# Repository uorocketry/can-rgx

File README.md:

# uORocketry CAN-RGX 2021

This is the uORocketry code for the 2021 Canadian Reduced Gravity Experiment Design Challenge (CAN-RGX).

This repository consists of the code of three components:
- Raspberry Pi (mainRPI.py): In charge of monitoring the experiment and controlling various components on user request.
- Control GUI (mainLaptop.py): Connects to the RPi and provides a GUI to the user for monitoring and controlling the experiment.
- Teensy (teensy/): Communicates with the RPi. Controls and monitors the motors and photodiodes.

Together, these components control and monitor a heater, motors, high-powered LEDs, and sensors. Here is an overview of all of those systems together:

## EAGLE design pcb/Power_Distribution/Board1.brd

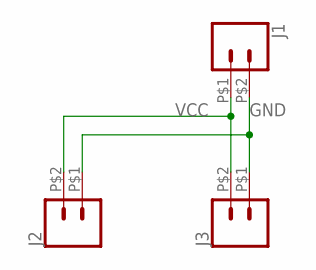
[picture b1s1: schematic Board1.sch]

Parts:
J1, J2, J3: CONN_02PTH2; 1X02_BIG

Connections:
GND: J1.P$2 (2), J2.P$1 (1), J3.P$1 (1)
VCC: J1.P$1 (1), J2.P$2 (2), J3.P$2 (2)

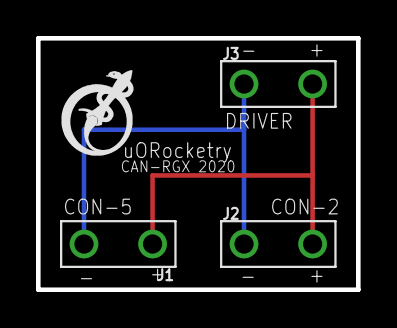
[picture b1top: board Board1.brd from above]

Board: 2 copper layers, 17.8 x 14.0 mm, 3 parts (0 on the bottom side), 2 nets.

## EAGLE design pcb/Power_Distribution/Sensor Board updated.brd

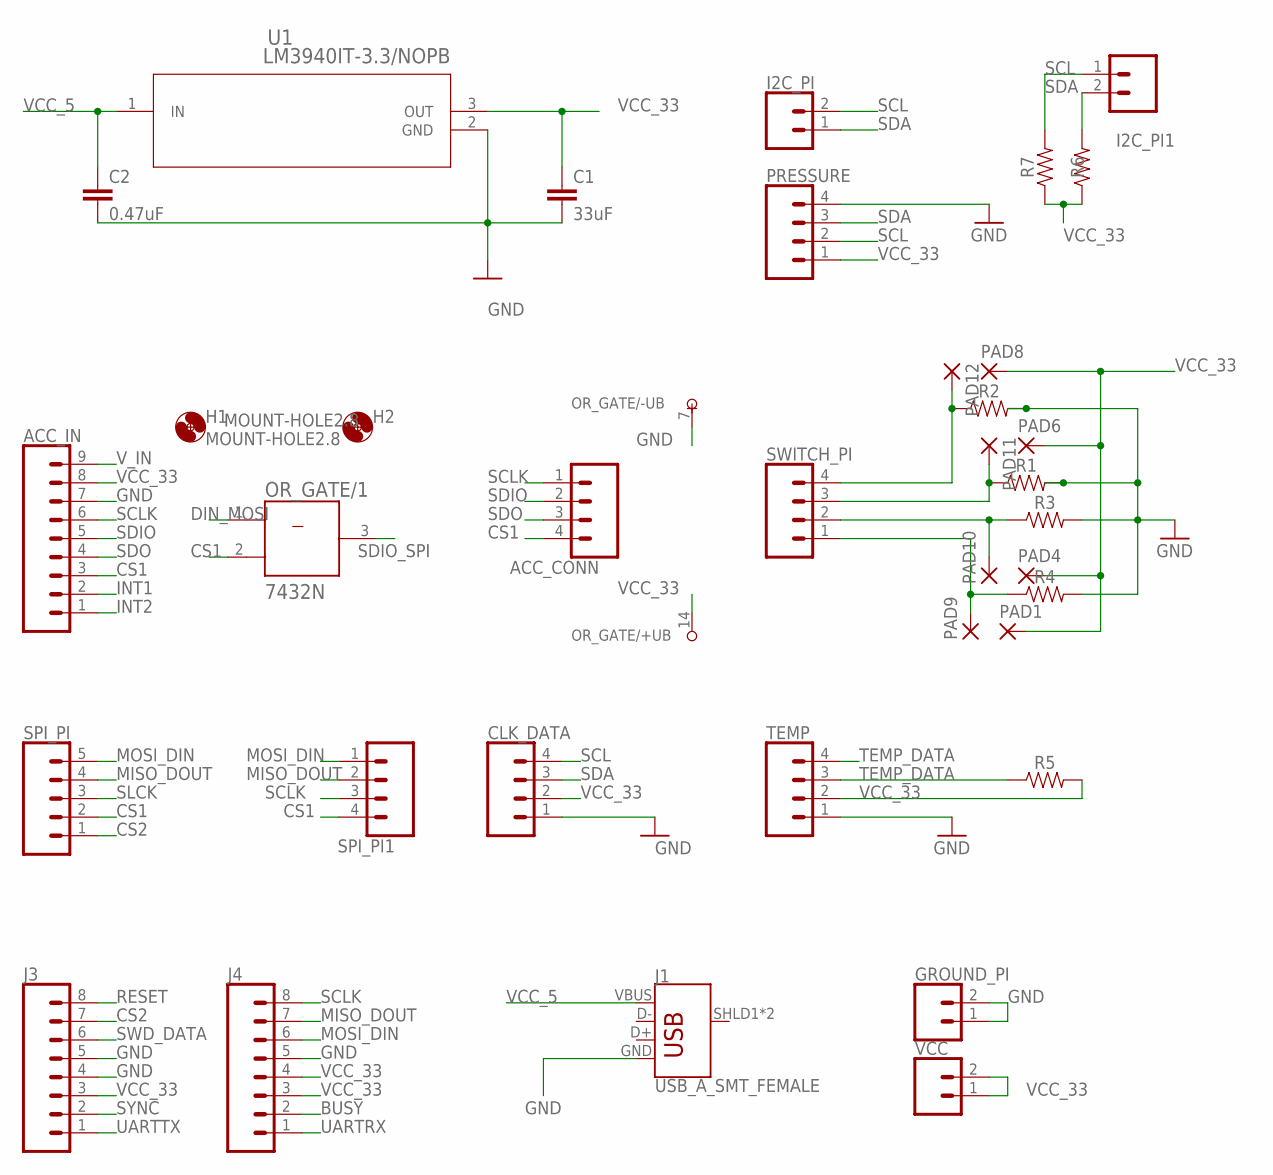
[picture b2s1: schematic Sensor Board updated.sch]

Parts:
ACC_CONN: CONN_04; 1X04
ACC_IN: CONN_09; 1X09
C1: 33uF; C2.5-4
C2: 0.47uF; C2.5-4
CLK_DATA: CONN_04; 1X04
GROUND_PI: CONN_02; 1X02
H1, H2: MOUNT-HOLE2.8; 2,8
I2C_PI, I2C_PI1: CONN_02; 1X02
J1: USB_A_SMT_FEMALE; USB-A-S-SILK-FEMALE
J3, J4: CONN_08"; 1X08
OR_GATE: 7432N; DIL14
PAD1, PAD4, PAD6, PAD8, PAD9, PAD10, PAD11, PAD12: 1,6/0,8
PRESSURE: CONN_04; 1X04
R1, R2, R3, R4, R5, R6, R7: AXIAL-0.3
SPI_PI: CONN_05; 1X05
SPI_PI1: CONN_04; 1X04
SWITCH_PI: CONN_04; 1X04
TEMP: CONN_04; 1X04
U1: LM3940IT-3.3/NOPB; T03B
VCC: CONN_02; 1X02

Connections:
BUSY: J4.2
CS1: ACC_CONN.4, ACC_IN.3, OR_GATE.2 (B), SPI_PI.2, SPI_PI1.4
CS2: J3.7, SPI_PI.1
DIN_MOSI: OR_GATE.1 (A)
GND: ACC_IN.7, C1.2, C2.2, CLK_DATA.1, GROUND_PI.1, GROUND_PI.2, J1.GND, J3.4, J3.5, J4.5, OR_GATE.7 (-UB), PRESSURE.4, R1.P$2 (2), R2.P$2 (2), R3.P$2 (2), R4.P$2 (2), TEMP.1, U1.2 (GND)
INT1: ACC_IN.2
INT2: ACC_IN.1
MISO_DOUT: J4.7, SPI_PI.4, SPI_PI1.2
MOSI_DIN: J4.6, SPI_PI.5, SPI_PI1.1
unnamed: PAD10.1, R3.P$1 (1), SWITCH_PI.2
unnamed: PAD9.1, R4.P$1 (1), SWITCH_PI.1
unnamed: PAD11.1, R1.P$1 (1), SWITCH_PI.3
unnamed: PAD12.1, R2.P$1 (1), SWITCH_PI.4
RESET: J3.8
SCL: CLK_DATA.4, I2C_PI.2, I2C_PI1.1, PRESSURE.2, R7.P$2 (2)
SCLK: ACC_CONN.1, ACC_IN.6, J4.8, SPI_PI1.3
SDA: CLK_DATA.3, I2C_PI.1, I2C_PI1.2, PRESSURE.3, R6.P$2 (2)
SDIO: ACC_CONN.2, ACC_IN.5
SDIO_SPI: OR_GATE.3 (Y)
SDO: ACC_CONN.3, ACC_IN.4
SLCK: SPI_PI.3
SWD_DATA: J3.6
SYNC: J3.2
TEMP_DATA: R5.P$1 (1), TEMP.3, TEMP.4
UARTRX: J4.1
UARTTX: J3.1
VCC_5: C2.1, J1.VBUS, U1.1 (IN)
VCC_33: ACC_IN.8, C1.1, CLK_DATA.2, J3.3, J4.3, J4.4, OR_GATE.14 (+UB), PAD1.1, PAD4.1, PAD6.1, PAD8.1, PRESSURE.1, R5.P$2 (2), R6.P$1 (1), R7.P$1 (1), TEMP.2, U1.3 (OUT), VCC.1, VCC.2
V_IN: ACC_IN.9

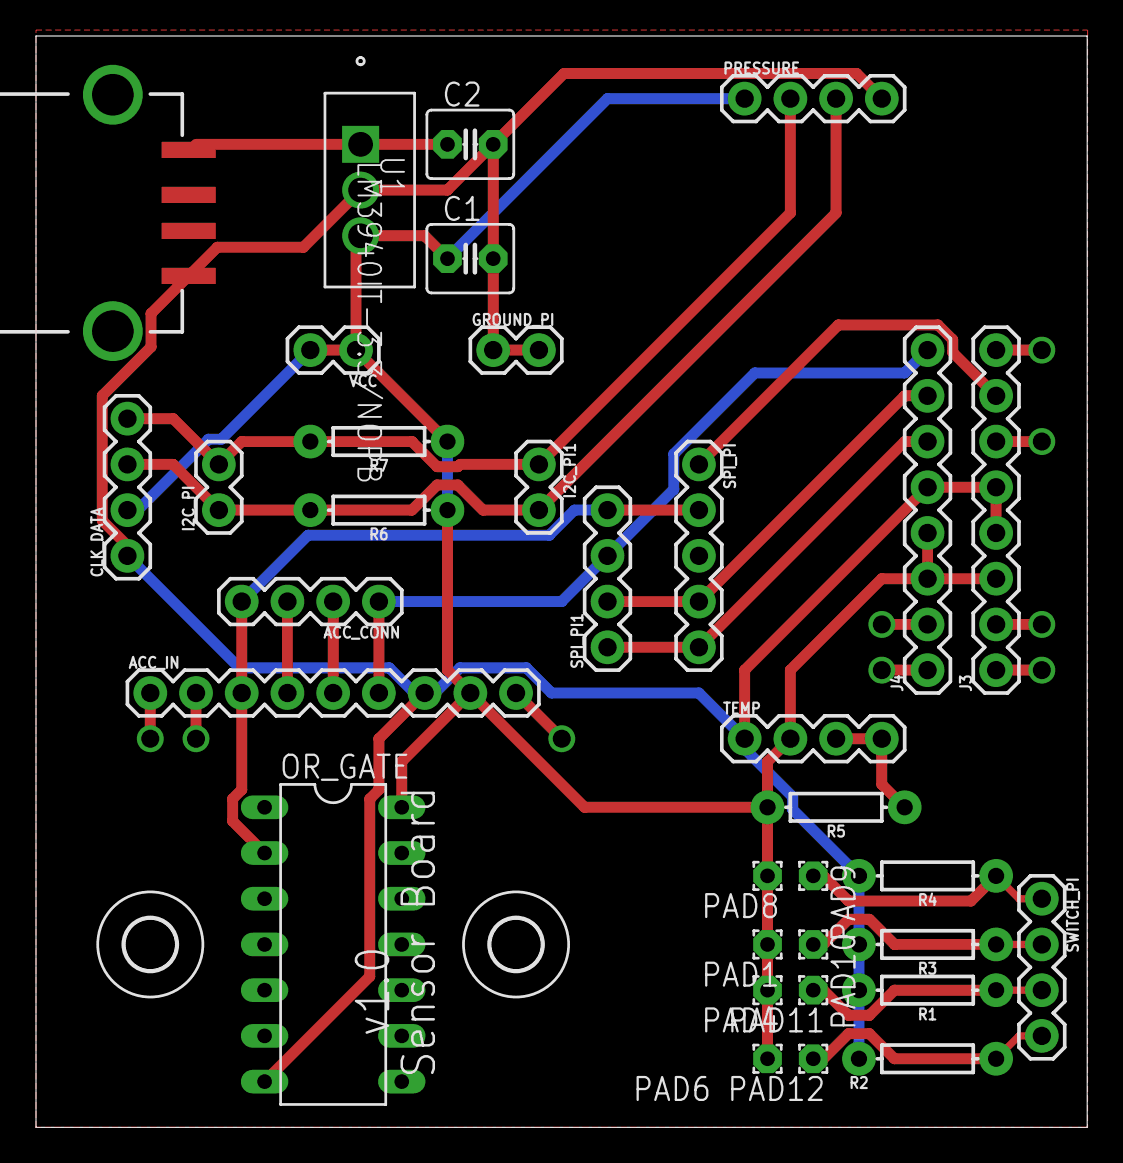
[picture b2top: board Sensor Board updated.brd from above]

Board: 2 copper layers, 58.4 x 60.6 mm, 36 parts (0 on the bottom side), 17 nets.

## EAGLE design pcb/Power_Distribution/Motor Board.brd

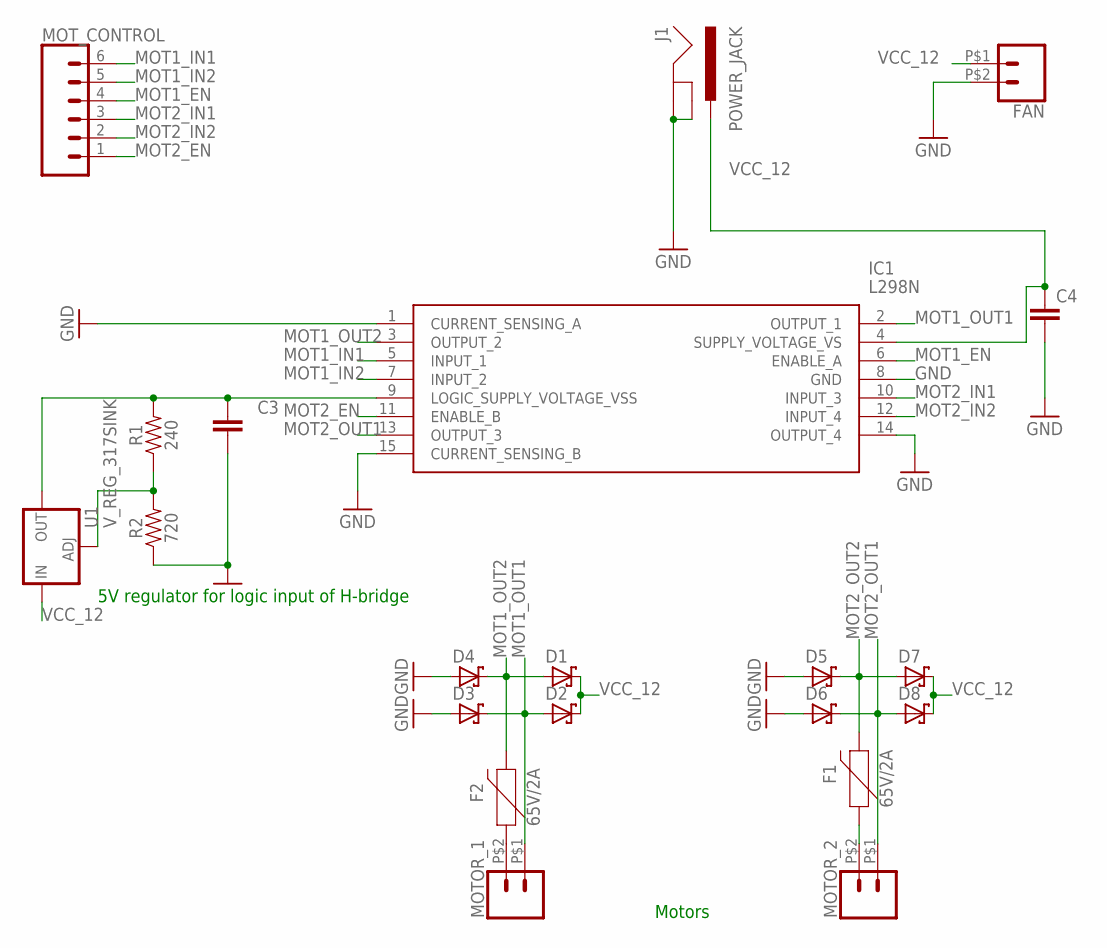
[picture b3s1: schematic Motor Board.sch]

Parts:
C3, C4: C5/5; C5B5
D1, D2, D3, D4, D5, D6, D7, D8: SCHOTTKY-DIODEC4111-15; C4111-15
F1, F2: 65V/2A; PTH
FAN: CONN_02PTH2; 1X02_BIG
IC1: L298N; MULTIWATT15V_1
J1: POWER_JACK; POWER_JACK_PTH
MOTOR_1, MOTOR_2: CONN_02PTH2; 1X02_BIG
MOT_CONTROL: CONN_06SILK_FEMALE_PTH; 1X06
R1: 240; AXIAL-0.3
R2: 720; AXIAL-0.3
U1: V_REG_317SINK; TO220-ADJ

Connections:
GND: C3.2, C4.2, D3.A, D4.A, D5.A, D6.A, FAN.P$2 (2), IC1.1 (CURRENT_SENSING_A), IC1.8 (GND), IC1.14 (OUTPUT_4), IC1.15 (CURRENT_SENSING_B), J1.GND, J1.GNDBREAK, R2.P$1 (1)
MOT1_EN: IC1.6 (ENABLE_A), MOT_CONTROL.4
MOT1_IN1: IC1.5 (INPUT_1), MOT_CONTROL.6
MOT1_IN2: IC1.7 (INPUT_2), MOT_CONTROL.5
MOT1_OUT1: D2.A, D3.C, IC1.2 (OUTPUT_1), MOTOR_1.P$1 (1)
MOT1_OUT2: D1.A, D4.C, F2.P$2 (2), IC1.3 (OUTPUT_2)
MOT2_EN: IC1.11 (ENABLE_B), MOT_CONTROL.1
MOT2_IN1: IC1.10 (INPUT_3), MOT_CONTROL.3
MOT2_IN2: IC1.12 (INPUT_4), MOT_CONTROL.2
MOT2_OUT1: D6.C, D8.A, IC1.13 (OUTPUT_3), MOTOR_2.P$1 (1)
MOT2_OUT2: D5.C, D7.A, F1.P$2 (2)
unnamed: F2.P$1 (1), MOTOR_1.P$2 (2)
unnamed: F1.P$1 (1), MOTOR_2.P$2 (2)
unnamed: C3.1, IC1.9 (LOGIC_SUPPLY_VOLTAGE_VSS), R1.P$2 (2), U1.OUT
unnamed: R1.P$1 (1), R2.P$2 (2), U1.ADJ
VCC_12: C4.1, D1.C, D2.C, D7.C, D8.C, FAN.P$1 (1), IC1.4 (SUPPLY_VOLTAGE_VS), J1.PWR, U1.IN

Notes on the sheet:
5V regulator for logic input of H-bridge
Motors

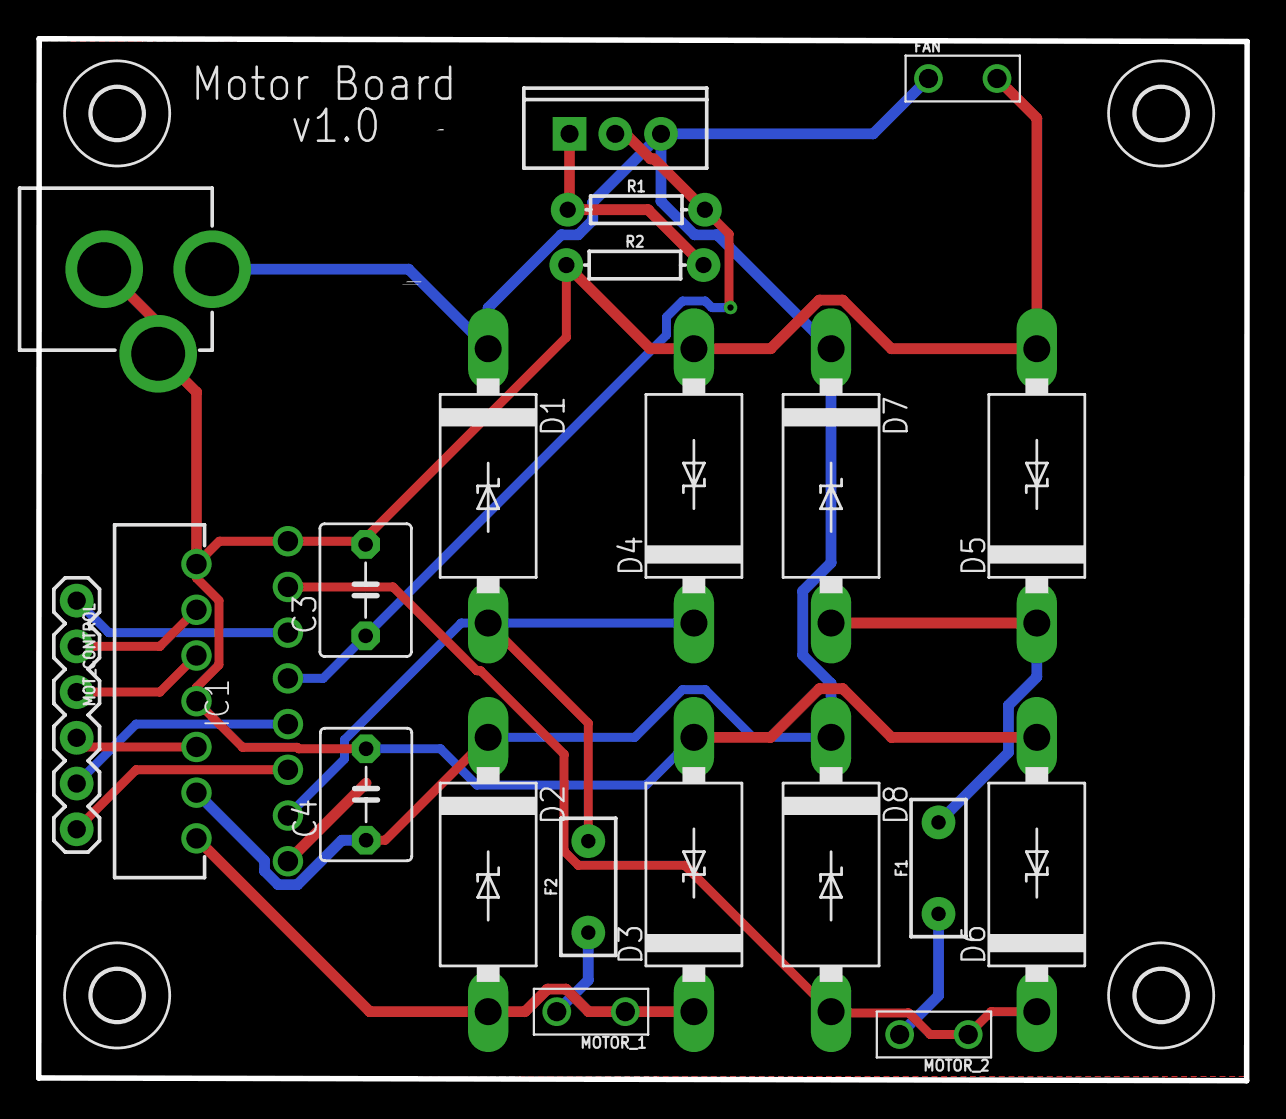
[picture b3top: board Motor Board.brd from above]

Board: 2 copper layers, 67.1 x 57.9 mm, 25 parts (0 on the bottom side), 16 nets.

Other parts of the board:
U$2, U$3, U$4, U$5: 2,8

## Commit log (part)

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2020-02-29 Added .gitignore
2020-03-07 Started code for thermometer sensor
2020-04-17 Added superclass BaseSensor for code common to all sensors
2020-04-19 Setup main logging under logger rpi.*
    This commit setups logging under Python's logging library. More specifically, any
    time Python's logging is used, the message will be outputed to the
    console (stdout) and to a file under logs/main. The file is named
    "log_(current date and time).log" and a new file is created for each run
    of the program. Furthermore, the logs follow this format:
    (date + time) - (logger's name) - (logging level) - (message)
2020-04-25 Use logging library to log data from sensors
    The Python's logging library is now used for logging data from sensors.
    The logs location for any sensor data is in logs/sensor/{name of sensor},
    with the file being a csv file. The abstract class SensorLogging handles
    all the initialization for each sensor type, so it would be best if all
    sensors' classes are a subclass of SensorLogging.
    A filter to the root logger as been added for sensor logging. This means
2020-04-25 Use standard logging system for thermometers
    With this commit, ThermoList implements the logging_loop() function and
    does the data logging under the logging.thermometer logger. To make sure
    each thermometer is read at its fastest rate, the logging_loop() of ThermoList
    actually creates a seperate thread running logging_loop() for each Thermo object.
2020-04-28 Setup logs output in the GUI
    Added a window which shows the logs to the user. Each log is color coded
    depending on its level:
    INFO and DEBUG : Black
    WARNING : Blue
    ERROR : Red
2020-04-28 Add status display to GUI
    Added a new window with a status indicator. This indicator is by default
    green, and will change color if a message is logged with a level of
    WARNING or ERROR. Furthermore, for these levels, the indicator will
    flash to be more apparent to the user. The indicator can be cleared back
    to green using a button.
2020-04-28 Add control of motors and LEDs in GUI
2020-04-30 Implement TCP socket server on RPI
    Implemented a simple, single threaded server for the RPI. Eventually,
    the laptop will connect to this server to control various elements of
    the experiment.
2020-05-01 Create socket server on laptop to receive logs
    Implement a simple TCP server on the laptop for the logging. It handles
    only one connected client at a time. When it receives data, it will
    unpickle it and log it using the logger specified in the record's name.
2020-05-01 Standardize and improve naming format for log files
    Change the folder structure of log files to be in this format (folder2
    is optional):
    logs/{device}/{folder}[/{folder2}]/{device}.{folder(2)}_{time}.type
    The goal is to make everything consistent and make it clear from where
    each log file comes from. This format is enforced by the MakeFileHandler
    class.
2020-05-01 Handle ConnectionResetError in laptop's logging receiver
2020-05-01 Use config file for IP addresses
    Use a file called 'config.ini' to save the IP and port for the RPI and
    laptop. If the file doesn't exist, it will be created using the default
    values.
    Please note 'config.ini' is ignored by git. Because of this, different
    computers can have different config files without being bothered by git.
2020-05-01 Fix laptop not creating sensor log files
    Add checks when the logging receiver receives a log with the logger name
    starting with 'sensorlog'. If this is the case, it will then check if it
    has a handler attached, and create it if this is not the case.
    The end result is that the log files follow the same format as the RPI,
    where there is a seperate file for each sensor.
2020-05-01 Implement a loop that continously ping the RPI
    While there is a constant communication between the RPI and laptop for
    the logs, messages to control the motors and LEDs will be more sparse.
    To prevent surprises when a control message is sent, the laptop will
    regularly ping the RPI to make sure communication is fine. If there is a
    problem, user is alerted.
2020-05-18 Use config file for laptop's IPs
2020-05-23 Start the Vibration class and add functions to read and write to sensor
2020-05-23 Add registers values for the vibration sensor
2020-05-23 Setup sensor's registers to use it in MFFT mode
2020-05-23 Implement the logging loop for the vibration sensor
2020-05-23 Add check if the sensor is not connected
    The register PROD_ID contains a known value from the sensor. This adds a
    check to see if the value is indeed was is expected. If the value
    returned is not as expected, it may mean that the sensor is disconnected
    or that a different kind of sensor is connected.
2020-05-30 Incomplete pressure file
2020-06-21 Fix issues when logging errors in the __init__ of the vibration class
2020-06-21 Use multiprocessing instead of threading
2020-06-21 Move the setup of each sensor to the child processes
2020-06-21 Monitor child processes and restart them in case they quit
2020-06-29 Cleanup code
2020-06-29 Revert code cleanup for pressure.py
2020-06-29 Testing acceleration
2020-06-29 Add conversion
2020-06-30 Fix error in config configuration
2020-07-04 Fix pressure sensor code
2020-07-04 Update range
2020-07-24 Set the allow_reuse_address option to prevent errors when restarting quickly the TCP servers
2020-07-26 Add timeout when laptop is connecting to the RPi
2020-07-26 Implement the LED control on the RPi when receiving a CONTROLLED message
2020-07-26 Implement the LED control on the laptop
2020-07-29 Use the ErrorManager in mainRPI.py
2020-07-29 Add support for reusing the same error_id across different ErrorManager instances
2020-07-29 Fix issue of status indicator flashing like crazy when multiple errors are active at the same time
    Before, each time an error was logged, flash_status() would get called even if the indicator was flashing before. This would make multiple flash_status run at the same time, causing some rapid flashi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
2020-07-29 Add option to ErrorManager to resend an error after a certain amount of time
2020-08-10 Start the Arduino code to control the motors. The limit switches are not implemented yet
2020-08-10 Periodically send an informational message about the motors' state when DEBUG is set
2020-08-11 Change motors' ports to valid ones
2020-08-11 Add a check if a motor runs for too long
2020-08-13 Implement a way to request the motor state on the Arduino
2020-08-15 Change (again) the pin numbers to valid ones
    There seems to be an issue that pin 0 and 1 can't be used for limit switches because they are probably the Serial pins
2020-08-15 Cleanup and remove useless debug print statements in the i2c interrupt
    Serial print statements do not work in interrupts
2020-09-09 pid control value change
2020-09-09 Temperature management initial commit
2020-09-09 pid cleanup
2020-09-09 temp sensor dummy
2020-09-09 temperature sensor modified
2020-09-09 fix acceptable error range
2020-09-09 call pid method
2020-09-09 import thermometer module
2020-09-23 Change the SPI max clock to 1 MHz
    5Mhz is the maximum clock speed. However, because having high clock speeds seems to complicate things a bit (see 'Retrieving Data from FIFO' in the datasheet), we'll set it lower for now
2020-09-23 Make sure the code uses a active low CS
2020-11-11 Lower the LED intensity
2020-11-11 Use the ErrorManager in pingchecker.py
2021-01-07 Add comment to the Thermometer class
2021-01-07 Fix formatting in mainLaptop.py
2021-01-07 Add comment to setup_logging() in SensorLogging
2021-01-09 Fix typo in loggingreceiver.py
2021-01-14 Fix typo in pingchecker.py
2021-01-22 Updated thread to retrieve current temperature reading.
2021-02-15 Significant changes to acceleration code
2021-02-15 Implement queue to read data passed from thermometer thread
2021-02-16 Refactor code to make it clearer
2021-02-16 Add and fix comments
2021-02-16 Combine the values of all axis in one row for the vibration sensor
2021-02-16 Fix #26: Use Regex to read from temperature sensors
    This also fixes #27
2021-02-16 Move Arduino code to `src-old`
2021-02-16 Finish porting code to the Teensy
2021-02-16 Allow the Teensy to send the LED state via i2c
2021-02-16 Create the Teensy class to communicate with the microcontroller
2021-02-16 Use the ErrorManager in MotorControl
2021-02-16 Fix incorrect import
2021-02-16 Add some more thermometer sensors
2021-02-18 Redo xfer_write_byte method
2021-02-19 Implement exception handling for TypeError in received temperature data
2021-02-20 Improve exception handling message
2021-03-20 Add realtime graphing functionality for PID
2021-04-02 Add a simple script to control the motors
2021-04-09 Cleanup a bit temp_management.py
2021-04-30 Manually setup sensor logging on the laptop for each sensor
2021-04-30 Create the Sensors window and start adding some sensors
2021-05-09 Change GPIO pin value
2021-05-09 Move constants outside the Accelerometer class
2021-05-09 Cleanup get_acceleration_data()
2021-05-09 Fix #37
2021-05-10 Fix xfer_read_byte()
2021-05-10 Remove the unnecessary printing of the raw data
2021-05-11 Only read from the sensor when there is available data
2021-05-11 Round the output of the accelerometer
2021-05-11 Cleanup
2021-05-12 Addressed PR comments - Var name for relay pin and setpoint as global var.
2021-05-24 Update comments on sendI2CState()
2021-05-24 Rename variable
2021-06-13 Cleanup PID config file reading
2021-06-19 Update vibration BUSY pin
2021-06-20 Fix Teensy I2C
2021-06-20 Limit switches fixes
2021-06-22 Move common code to motor.cpp
2021-06-22 Add files to .gitignore
2021-06-22 Add DEBUG macro to debug build
2021-06-29 Add debug statements
2021-07-01 Added revertable changes for July 1st testing
2021-07-08 Start temp_management thread from mainRPI
2021-07-08 Revert "Start temp_management thread from mainRPI"
    This reverts commit 8c3f0971
2021-07-08 Enable temp_management thread
2021-07-08 Check the photodiodes on the RPi
2021-07-09 Check limit 100 times
2021-07-10 Correct setpoint
2021-07-11 Fix bug in error manager
    The incorrect logger was being used when resolving, causing it to log
    under `root`
2021-07-11 Stop spamming the logs in temp_management
2021-07-11 Clarify temperature resove message
2021-07-12 Add sleep before starting temp management
2021-07-12 Add better error handling when dealing with the Teensy
2021-07-12 LED fixes
2021-07-12 Stop spamming on high temperature
2021-07-12 Cleanup logs when starting motor
2021-07-12 Fix retrieving state from Teensy
2021-07-13 Move MotorDirection to its own file
2021-07-13 Remove the unused vibration status for now
2021-07-13 Fix average temperature in GUI
2021-07-14 Use the blocking feature of the logging queue
2021-07-14 Add a time.sleep to temp_management
2021-07-14 Remove the debug statements in temp_management
2021-07-14 Fix the heater state
2021-08-06 Catch extra exception in thermometer
2021-08-06 Initializing new branch for accelerometer using i2c.
2021-08-06 Implemented I2C protocol for ADXL343 accelerometer.
2021-08-07 Improve error handling of thermometer
2021-08-07 Add pressure frame
2021-08-07 Fix error with waiting for sensor to connect statement.
2021-08-07 Change output data rate to 200Hz to match 100kHz Rpi I2C freq.
2021-08-07 Fix accelerometer
2021-08-07 Lower range for accelerometer
2021-08-07 Enable pull up for GPIO 4
2021-08-08 Remove debug print
2021-08-08 Put proper temperature names
2021-08-08 Round the average temperature
2021-08-08 Add foam sensor
2021-08-08 Fix LED error
2021-08-08 Switch photodiodes to use pull up resistors
2021-08-08 Change photodiode threshold
2021-08-08 Fix LED state
2021-08-12 Log accelerometer on the laptop
2021-08-12 Add retry when communicating to Teensy
    Fix #49
2021-08-12 Fix pressure sensor value
2021-08-12 Remove reference to Vibration sensor
2021-08-12 Add countdown before activating the LEDs
2021-08-12 Clarify errors when the DMX controller is not connected
2021-08-12 Stop spamming logs with pressure sensor
2021-08-12 Re-initializing backup pressure sensor code for new sensor BMP388 using I2C.
2021-08-12 Read output from pressure sensor registers and calibrate using compensation coefficients.
2021-08-13 Add keybinds for motor
2021-08-13 Add statement to mainRPI.py to call backup pressure sensor class.
2021-08-14 Change LED time and power
2021-08-14 Switch to use Serial
2021-08-14 Start to use serial for Teensy communication
2021-08-14 Change motor timeout
2021-08-14 Clarify motor timeout message
2021-08-15 Add flexibility when connecting to Teensy
2021-08-15 Fix compile warning
2021-08-15 Reset serial if we can't talk to Teensy
2021-08-15 Allow error messages to be sent again for LEDs
2021-08-16 Change motor timeout to 60 seconds
2021-08-16 Fix incorrect motor reporting
2021-09-10 Fix bug outputting incorrect timestamps for acceleration sensor
2021-09-13 Center image

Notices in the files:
parts and their libraries:
SparkFun-Connectors: Licensing: Creative Commons ShareAlike 4.0 International - https://creativecommons.org/licenses/by-sa/4.0
